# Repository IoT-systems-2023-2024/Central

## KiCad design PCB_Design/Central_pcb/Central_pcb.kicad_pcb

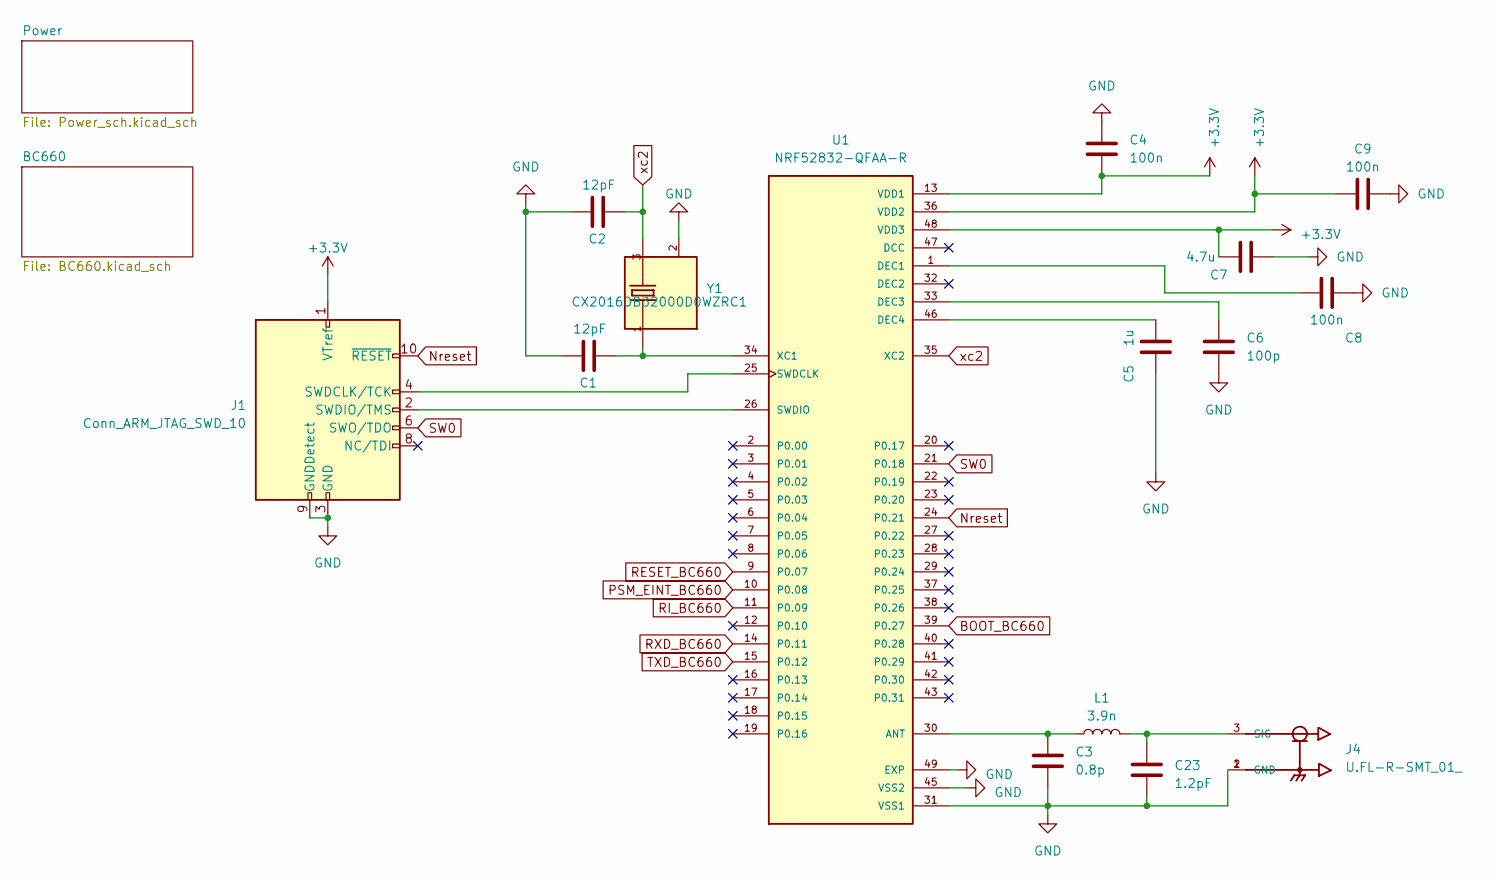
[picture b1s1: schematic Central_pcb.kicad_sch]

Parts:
C1, C2: 12pF; C_0805_2012Metric_Pad1.18x1.45mm_HandSolder
C3: 0.8p; C_0603_1608Metric_Pad1.08x0.95mm_HandSolder
C4, C8, C9: 100n; C_0805_2012Metric_Pad1.18x1.45mm_HandSolder
C5: 1u; C_0805_2012Metric_Pad1.18x1.45mm_HandSolder
C6: 100p; C_0805_2012Metric_Pad1.18x1.45mm_HandSolder
C7: 4.7u; C_0805_2012Metric_Pad1.18x1.45mm_HandSolder
C23: 1.2pF; C_0805_2012Metric_Pad1.18x1.45mm_HandSolder
J1: Conn_ARM_JTAG_SWD_10; PinSocket_2x05_P1.27mm_Vertical
J4: U.FL-R-SMT_01_; HRS_U.FL-R-SMT_01_
L1: 3.9n; C_0805_2012Metric_Pad1.18x1.45mm_HandSolder
U1: NRF52832-QFAA-R; QFN40P600X600X90-49N
Y1: CX2016DB32000D0WZRC1; OSCCC200X160X45N; PARTREV 00

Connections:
+3.3V: C4.1, C7.2, C9.1, J1.1 (VTref), U1.13 (VDD1), U1.36 (VDD2), U1.48 (VDD3); also elsewhere on the board
BOOT_BC660: U1.39 (P0.27); also elsewhere on the board
GND: C1.1, C2.1, C3.1, C4.2, C5.2, C6.2, C7.1, C8.2, C9.2, C23.1, J1.3 (GND), J1.5 (GND), J1.9 (GNDDetect), J4.1 (GND), J4.2 (GND), U1.31 (VSS1), U1.45 (VSS2), U1.49 (EXP), Y1.2; also elsewhere on the board
unnamed: J1.4 (SWDCLK/TCK), U1.25 (SWDCLK)
unnamed: J1.2 (SWDIO/TMS), U1.26 (SWDIO)
unnamed: C23.2, J4.3 (SIG), L1.2
unnamed: C3.2, L1.1, U1.30 (ANT)
unnamed: C8.1, U1.1 (DEC1)
unnamed: C6.1, U1.33 (DEC3)
unnamed: C5.1, U1.46 (DEC4)
unnamed: C1.2, U1.34 (XC1), Y1.1
Nreset: J1.10 (~RESET), U1.24 (P0.21)
PSM_EINT_BC660: U1.10 (P0.08); also elsewhere on the board
RESET_BC660: U1.9 (P0.07); also elsewhere on the board
RI_BC660: U1.11 (P0.09); also elsewhere on the board
RXD_BC660: U1.14 (P0.11); also elsewhere on the board
SW0: J1.6 (SWO/TDO), U1.21 (P0.18)
TXD_BC660: U1.15 (P0.12); also elsewhere on the board
xc2: C2.2, U1.35 (XC2), Y1.3

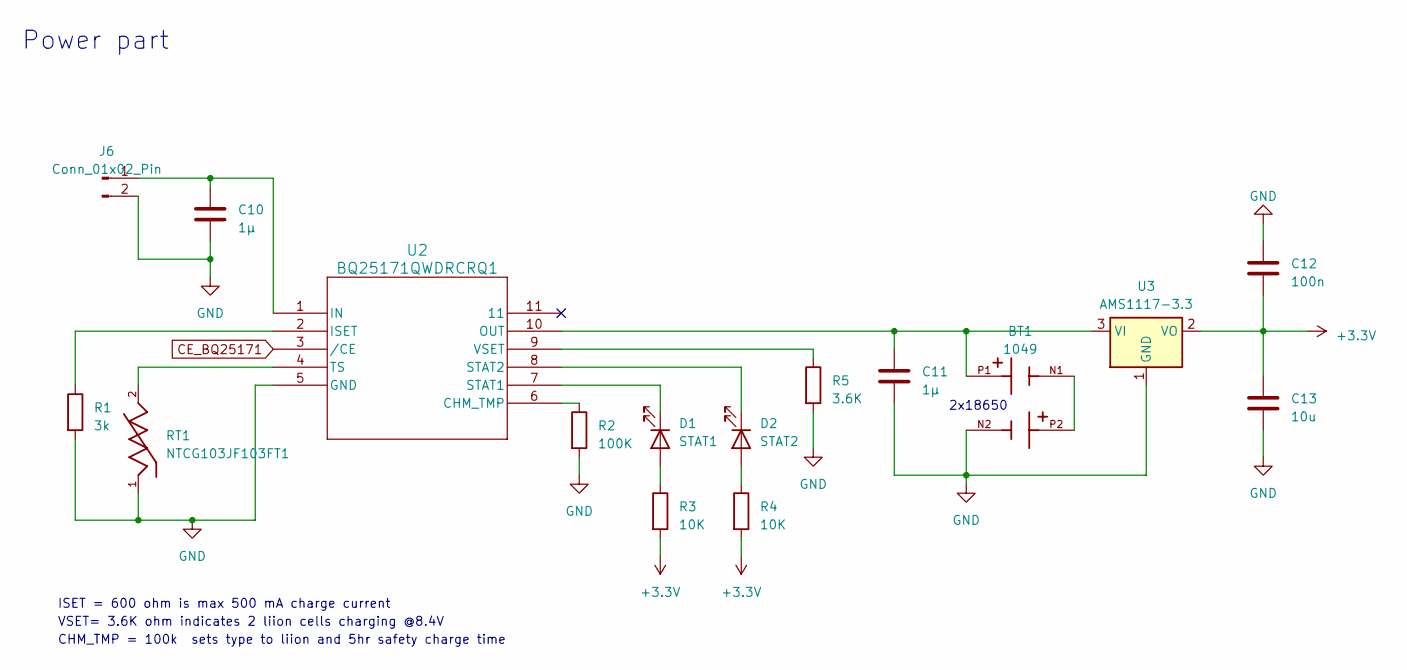
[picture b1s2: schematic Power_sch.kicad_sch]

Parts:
BT1: 1049; BAT_1049; PARTREV F
C10, C11: 1µ; C_0805_2012Metric_Pad1.18x1.45mm_HandSolder
C12: 100n; C_0805_2012Metric_Pad1.18x1.45mm_HandSolder
C13: 10u; C_0805_2012Metric_Pad1.18x1.45mm_HandSolder
D1: STAT1; LED_0805_2012Metric_Pad1.15x1.40mm_HandSolder
D2: STAT2; LED_0805_2012Metric_Pad1.15x1.40mm_HandSolder
J6: Conn_01x02_Pin; PinSocket_1x02_P2.54mm_Vertical
R1: 3k; R_0805_2012Metric_Pad1.20x1.40mm_HandSolder
R2: 100K; R_0805_2012Metric_Pad1.20x1.40mm_HandSolder
R3, R4: 10K; R_0805_2012Metric_Pad1.20x1.40mm_HandSolder
R5: 3.6K; R_0805_2012Metric_Pad1.20x1.40mm_HandSolder
RT1: NTCG103JF103FT1; THERM_NTCG103JF103FT1; PARTREV 8/12/2022
U2: BQ25171QWDRCRQ1; VSON10_BQ25171_3X3_TEX
U3: AMS1117-3.3; SOT-223-3_TabPin2

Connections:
+3.3V: C12.2, C13.1, R3.2, R4.2, U3.2 (VO); also elsewhere on the board
CE_BQ25171: U2.3 (/CE)
GND: BT1.N2, C10.2, C11.2, C12.1, C13.2, J6.2, R1.2, R2.2, R5.2, RT1.1, U2.5 (GND), U3.1 (GND); also elsewhere on the board
unnamed: BT1.N1, BT1.P2
unnamed: D1.2 (A), R3.1
unnamed: D1.1 (K), U2.7 (STAT1)
unnamed: D2.2 (A), R4.1
unnamed: D2.1 (K), U2.8 (STAT2)
unnamed: C10.1, J6.1, U2.1 (IN)
unnamed: R2.1, U2.6 (CHM_TMP)
unnamed: R1.1, U2.2 (ISET)
unnamed: BT1.P1, C11.1, U2.10 (OUT), U3.3 (VI)
unnamed: RT1.2, U2.4 (TS)
unnamed: R5.1, U2.9 (VSET)

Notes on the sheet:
ISET = 600 ohm is max 500 mA charge current
2x18650
VSET= 3.6K ohm indicates 2 liion cells charging @8.4V
Power part
CHM_TMP = 100k sets type to liion and 5hr safety charge time

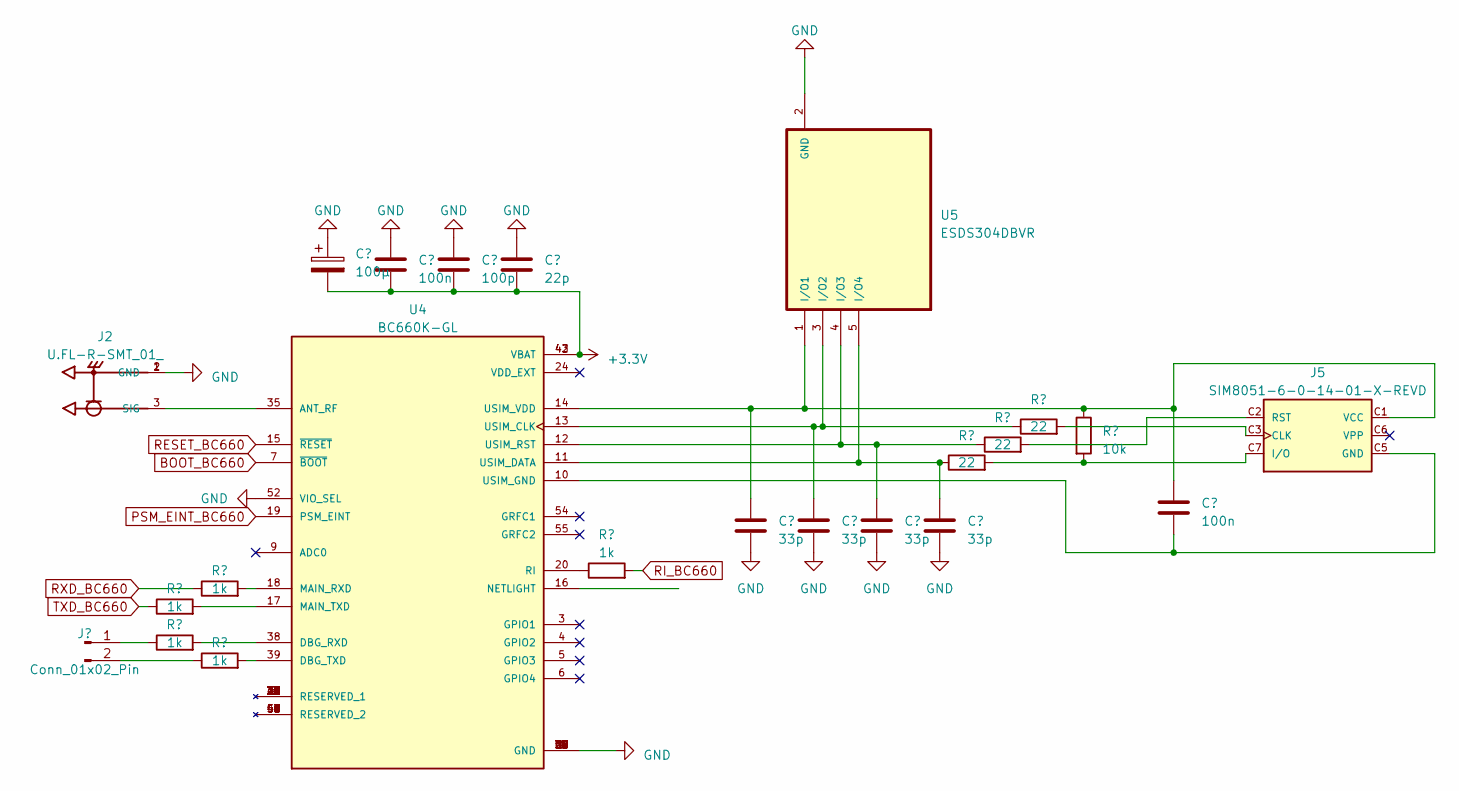
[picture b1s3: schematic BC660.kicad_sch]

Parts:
C14: 100µ; C_0805_2012Metric_Pad1.18x1.45mm_HandSolder
C15, C22: 100n; C_0805_2012Metric_Pad1.18x1.45mm_HandSolder
C16: 100p; C_0805_2012Metric_Pad1.18x1.45mm_HandSolder
C17: 22p; C_0805_2012Metric_Pad1.18x1.45mm_HandSolder
C18, C19, C20, C21: 33p; C_0805_2012Metric_Pad1.18x1.45mm_HandSolder
J2: U.FL-R-SMT_01_; HRS_U.FL-R-SMT_01_
J3: Conn_01x02_Pin; PinHeader_1x02_P2.54mm_Vertical
J5: SIM8051-6-0-14-01-X-REVD; GCT_SIM8051-6-0-14-01-X-REVD
R6, R7, R8, R9, R10: 1k; R_0805_2012Metric_Pad1.20x1.40mm_HandSolder
R11, R12, R13: 22; R_0805_2012Metric_Pad1.20x1.40mm_HandSolder
R14: 10k; R_0805_2012Metric_Pad1.20x1.40mm_HandSolder
U4: BC660K-GL; XCVR_BC660K-GL; PARTREV 1.2
U5: ESDS304DBVR; SOT95P280X145-5N

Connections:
+3.3V: C14.2, C15.2, C16.2, C17.2, U4.42 (VBAT), U4.43 (VBAT); also elsewhere on the board
BOOT_BC660: U4.7 (~BOOT); also elsewhere on the board
GND: C14.1, C15.1, C16.1, C17.1, C18.2, C19.2, C20.2, C21.2, J2.1 (GND), J2.2 (GND), U4.1 (GND), U4.27 (GND), U4.34 (GND), U4.36 (GND), U4.37 (GND), U4.40 (GND), U4.41 (GND), U4.52 (VIO_SEL), U4.56 (GND), U4.57 (GND), U4.58 (GND), U5.2 (GND); also elsewhere on the board
unnamed: J2.3 (SIG), U4.35 (ANT_RF)
unnamed: J3.1, R7.1
unnamed: J3.2, R9.1
unnamed: J5.C3 (CLK), R13.2
unnamed: C22.1, J5.C5 (GND), U4.10 (USIM_GND)
unnamed: J5.C7 (I/O), R11.2, R14.2
unnamed: J5.C2 (RST), R12.2
unnamed: C18.1, C22.2, J5.C1 (VCC), R14.1, U4.14 (USIM_VDD), U5.1 (I/O1)
unnamed: R7.2, U4.38 (DBG_RXD)
unnamed: R9.2, U4.39 (DBG_TXD)
unnamed: R8.2, U4.18 (MAIN_RXD)
unnamed: R6.2, U4.17 (MAIN_TXD)
unnamed: R10.1, U4.20 (RI)
unnamed: C19.1, R13.1, U4.13 (USIM_CLK), U5.3 (I/O2)
unnamed: C21.1, R11.1, U4.11 (USIM_DATA), U5.5 (I/O4)
unnamed: C20.1, R12.1, U4.12 (USIM_RST), U5.4 (I/O3)
PSM_EINT_BC660: U4.19 (PSM_EINT); also elsewhere on the board
RESET_BC660: U4.15 (~RESET); also elsewhere on the board
RI_BC660: R10.2; also elsewhere on the board
RXD_BC660: R8.1; also elsewhere on the board
TXD_BC660: R6.1; also elsewhere on the board

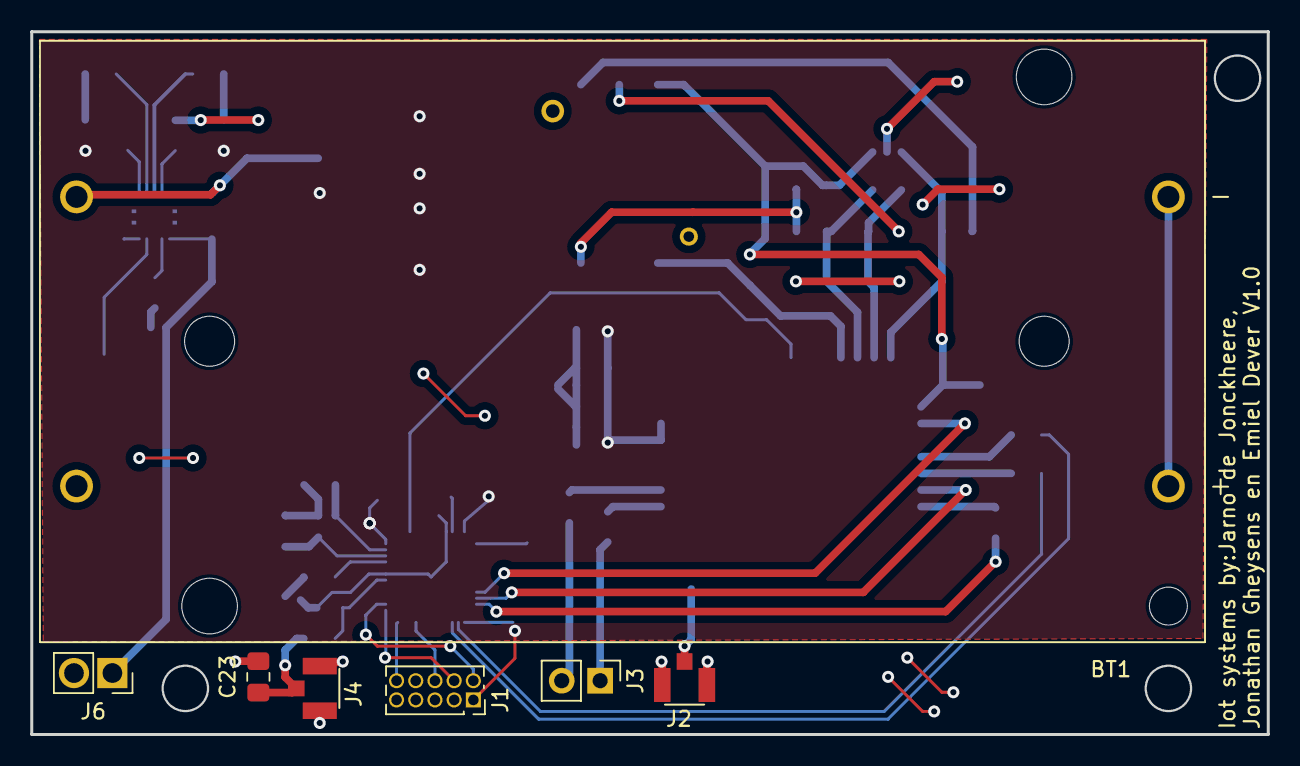
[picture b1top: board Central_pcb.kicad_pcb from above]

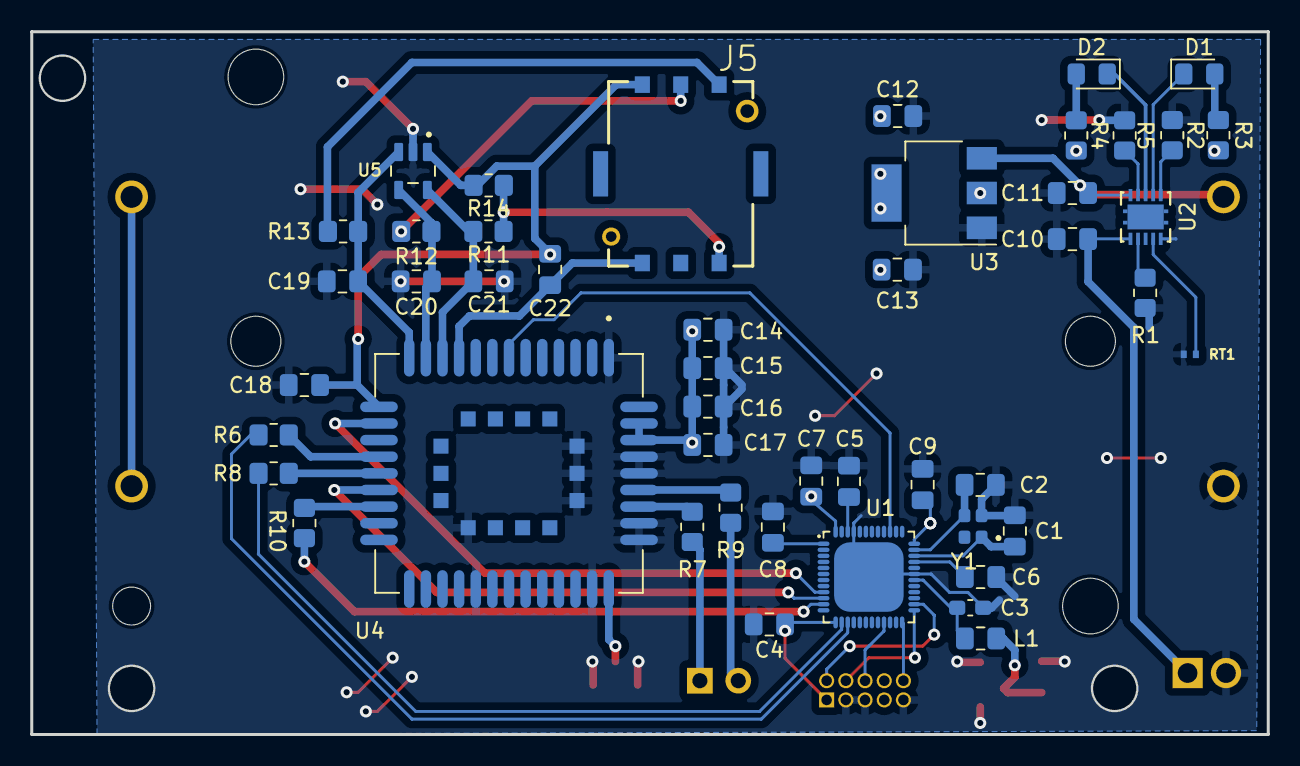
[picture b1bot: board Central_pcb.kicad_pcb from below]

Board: 2 copper layers, 81.8 x 46.5 mm, 54 parts (47 on the bottom side), 46 nets.

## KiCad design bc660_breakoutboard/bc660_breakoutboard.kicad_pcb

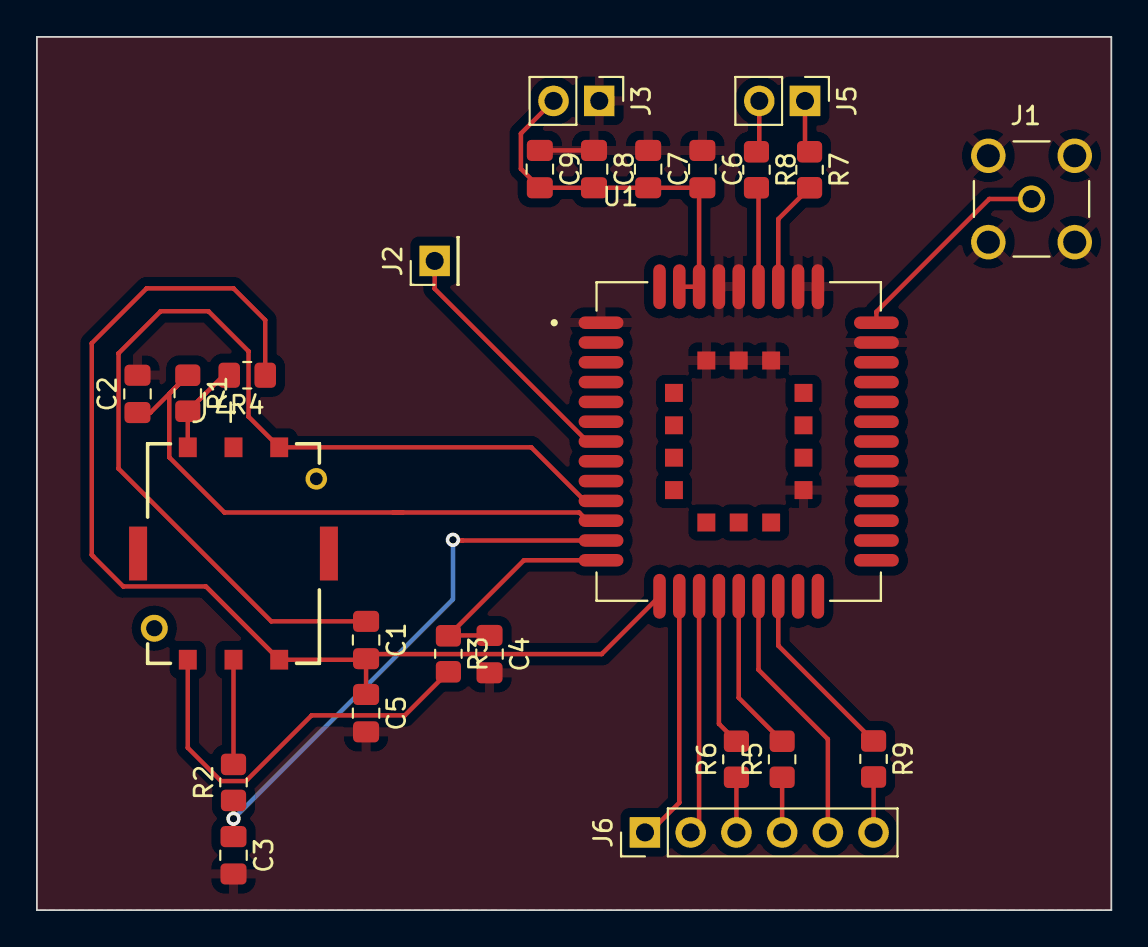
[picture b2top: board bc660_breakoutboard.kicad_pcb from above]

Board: 2 copper layers, 59.7 x 48.5 mm, 25 parts (0 on the bottom side), 25 nets.

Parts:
C1, C6: 100n; C_0805_2012Metric_Pad1.18x1.45mm_HandSolder
C2, C3, C4, C5: 33p; C_0805_2012Metric_Pad1.18x1.45mm_HandSolder
C7: 100p; C_0805_2012Metric_Pad1.18x1.45mm_HandSolder
C8: 22p; C_0805_2012Metric_Pad1.18x1.45mm_HandSolder
C9: 100µ; C_0805_2012Metric_Pad1.18x1.45mm_HandSolder
J1: SMA_CONNECTOR; LPRS_SMA_CONNECTOR
J2: Conn_01x01_Pin; PinHeader_1x01_P2.54mm_Vertical
J3, J5: Conn_01x02_Pin; PinHeader_1x02_P2.54mm_Vertical
J4: SIM8051-6-0-14-01-X-REVD; GCT_SIM8051-6-0-14-01-X-REVD
J6: Conn_01x06_Pin; PinHeader_1x06_P2.54mm_Vertical
R1, R2, R3: 22; R_0805_2012Metric_Pad1.20x1.40mm_HandSolder
R4: 10k; R_0805_2012Metric_Pad1.20x1.40mm_HandSolder
R5, R6, R7, R8, R9: 1k; R_0805_2012Metric_Pad1.20x1.40mm_HandSolder
U1: BC660K-GL; XCVR_BC660K-GL

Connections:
GND: C2.2, C3.2, C4.2, C5.2, C6.1, C7.1, C8.1, C9.1, J1.G1, J1.G2, J1.G3, J1.G4, J3.1, U1.1 (GND), U1.27 (GND), U1.34 (GND), U1.36 (GND), U1.37 (GND), U1.40 (GND), U1.41 (GND), U1.52 (VIO_SEL), U1.56 (GND), U1.57 (GND), U1.58 (GND)
unnamed: J2.1, U1.7 (~BOOT)
unnamed: C6.2, C7.2, C8.2, C9.2, J3.2, U1.42 (VBAT), U1.43 (VBAT)
unnamed: J4.C3 (CLK), R3.2
unnamed: C1.1, J4.C5 (GND), U1.10 (USIM_GND)
unnamed: J4.C7 (I/O), R1.2, R4.2
unnamed: J4.C2 (RST), R2.2
unnamed: C1.2, C5.1, J4.C1 (VCC), R4.1, U1.14 (USIM_VDD)
unnamed: J5.1, R7.1
unnamed: J5.2, R8.1
unnamed: J6.1, U1.15 (~RESET)
unnamed: J6.2, U1.16 (NETLIGHT)
unnamed: J6.3, R6.1
unnamed: J6.4, R5.1
unnamed: J6.5, U1.19 (PSM_EINT)
unnamed: J6.6, R9.2
unnamed: J1.1, U1.35 (ANT_RF)
unnamed: R7.2, U1.38 (DBG_RXD)
unnamed: R8.2, U1.39 (DBG_TXD)
unnamed: R5.2, U1.18 (MAIN_RXD)
unnamed: R6.2, U1.17 (MAIN_TXD)
unnamed: R9.1, U1.20 (RI)
unnamed: C4.1, R3.1, U1.13 (USIM_CLK)
unnamed: C2.1, R1.1, U1.11 (USIM_DATA)
unnamed: C3.1, R2.1, U1.12 (USIM_RST)

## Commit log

2023-11-02 add breakout board design
2023-11-03 update pcb design
2023-11-03 add footprints
2023-11-03 Initial setup
2023-11-03 Power part added
    Power part is finished with power footprints
2023-11-04 nrf52832 datasheet setup
2023-11-05 Scematic update
    update scematic and added some footrpints
2023-11-05 Change of crystal
2023-11-05 Added debug conn
2023-11-07 update pcb breakoutboard
2023-11-09 Initial PCB design
    Rough sketch of what the layout could be
2023-11-10 BLE testcode
2023-11-12 add bom
2023-11-12 PCB route
    Volledig geroute nog juist controleren en mounting holes doen + controleren dat er overal gnd en 3.3v mooi verbonden is
2023-11-12 Minur PCB update
2023-11-15 add csv file
2023-11-17 testprogramma_BLE
2023-11-17 Pcb Update
2023-12-20 UPDAATEEEE
2023-12-22 jfdqlk
2023-12-31 BLE_CODE
